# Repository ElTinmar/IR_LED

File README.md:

# IR_LED

This is an open-source infra-red illumnination solution (LED panel and driver) for machine vision.
An arduino nano every sits at the core of the driver board, and allows remote control from a PC through serial communication

The main features are: 

- infra-red LED panel, with 3 separately addressable concentric rings  
- manual or remote control of the brightness for the 3 channels
- LED driver can be strobed with the open-collector trigger output of a machine vision camera,
which significantly reduces heat output
- the temperature of the LED panel is measured in real time and can by controlled with a fan. 
The fan PWM can be set manually or via a software PID controller on the arduino

## hardware

PCB design files (Kicad v10)

## firmware

Arduino code (Arduino Nano Every)
 
## software

Python driver and GUI on the PC side

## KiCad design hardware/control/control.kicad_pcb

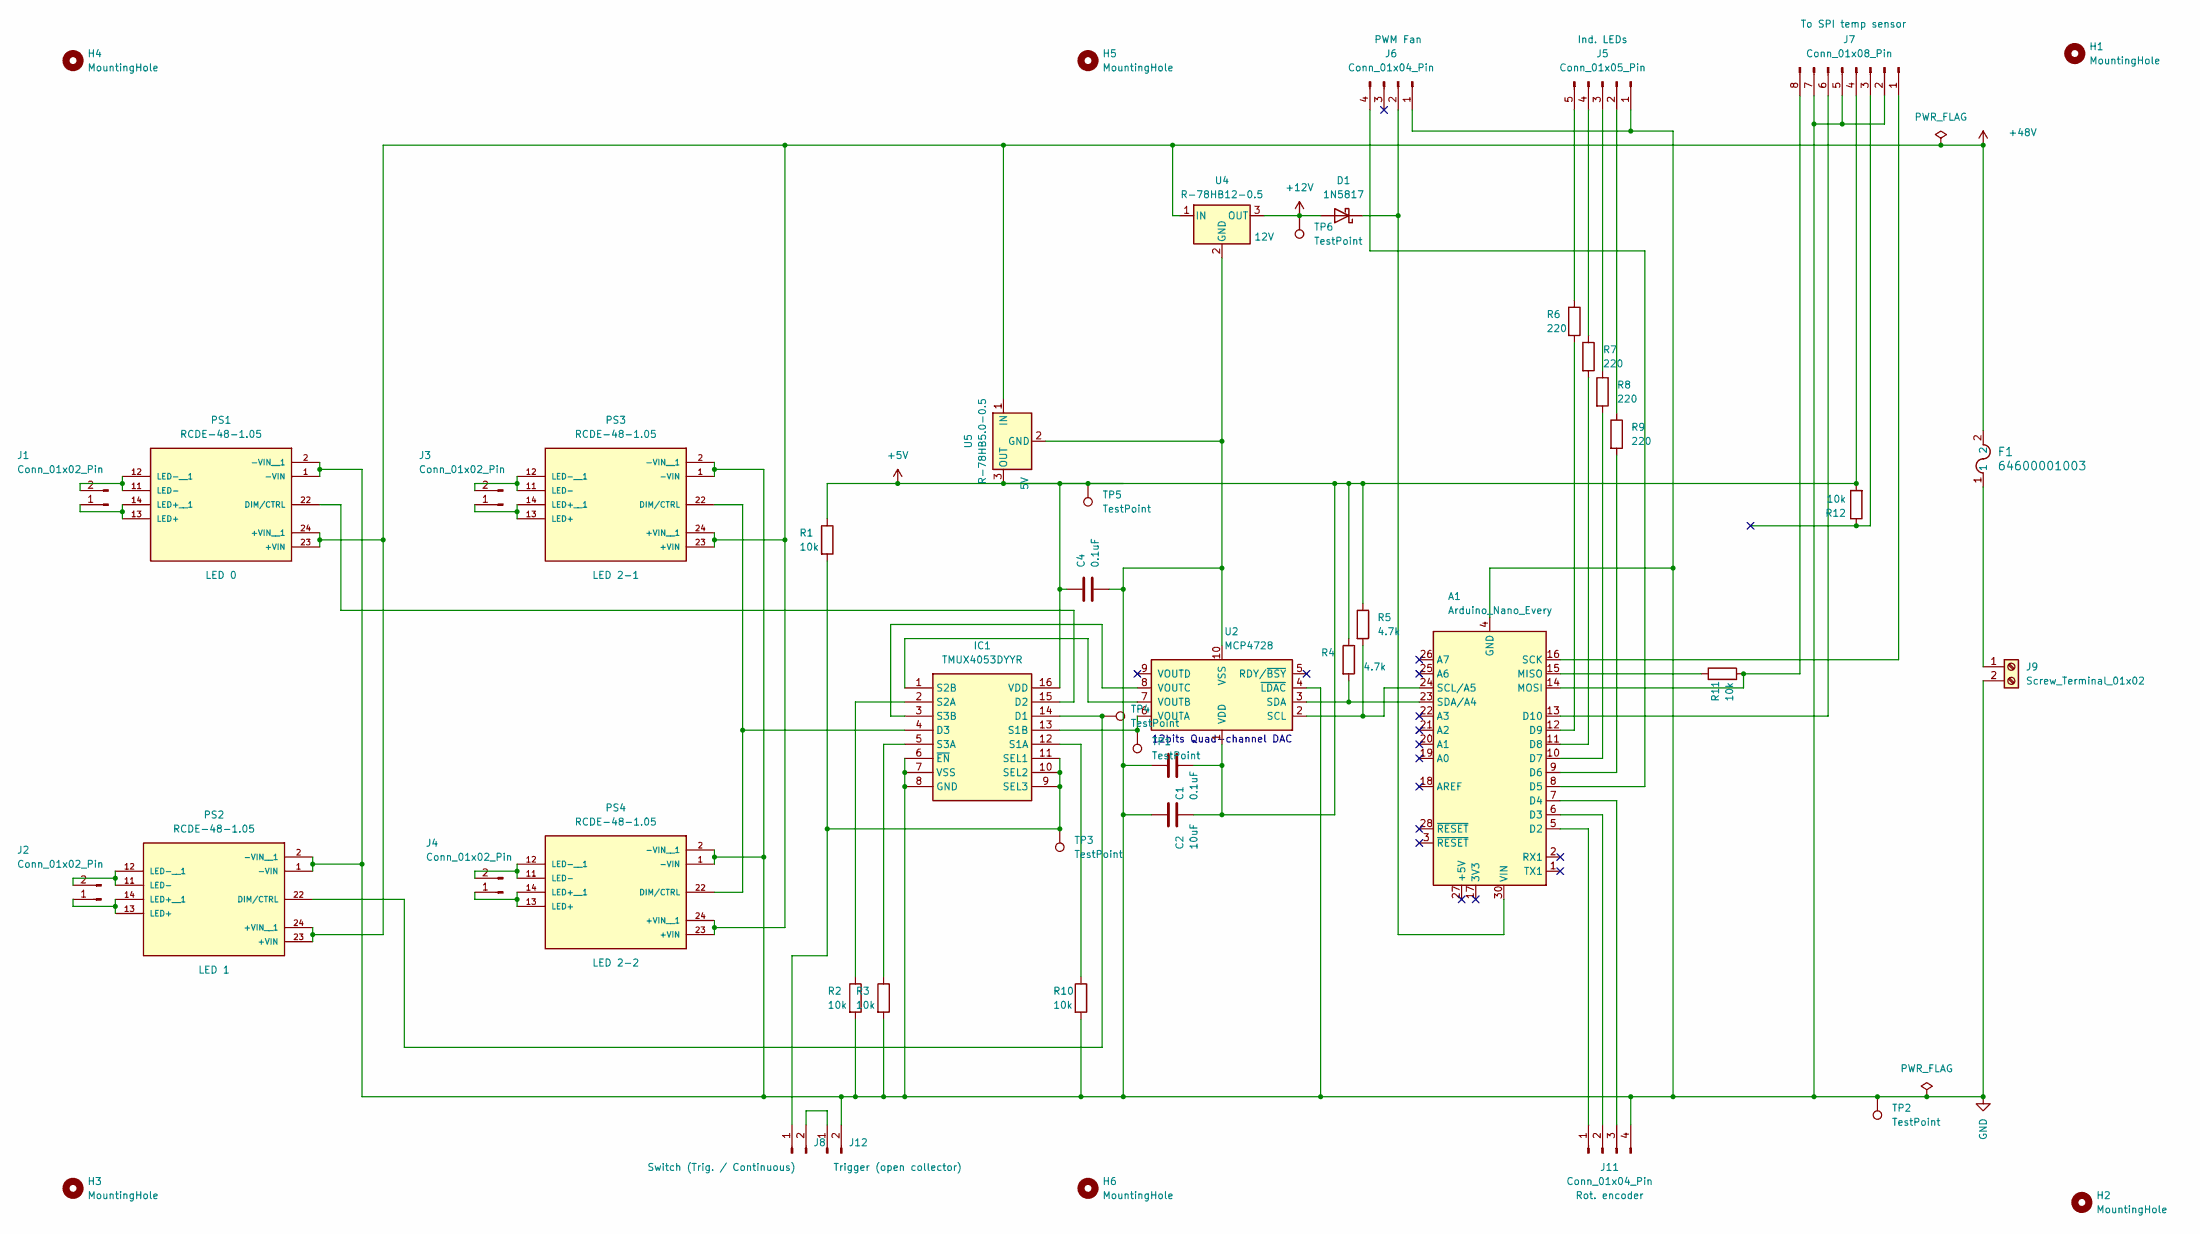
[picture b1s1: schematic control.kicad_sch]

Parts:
A1: Arduino_Nano_Every; Arduino_Nano
C1, C4: 0.1uF; C_Disc_D5.0mm_W2.5mm_P2.50mm
C2: 10uF; C_Disc_D5.0mm_W2.5mm_P2.50mm
D1: 1N5817; D_DO-41_SOD81_P10.16mm_Horizontal
F1: 64600001003; FUSE_646_1_LTF
H1, H2, H3, H4, H5, H6: MountingHole; MountingHole_3.2mm_M3
IC1: TMUX4053DYYR; SOP50P326X110-16N; Mouser Part Number 595-TMUX4053DYYR
J1, J2, J3, J4: Conn_01x02_Pin; Molex_Micro-Fit_3.0_43650-0200_1x02_P3.00mm_Horizontal
J5: Conn_01x05_Pin; Molex_KK-254_AE-6410-05A_1x05_P2.54mm_Vertical
J6, J11: Conn_01x04_Pin; Molex_KK-254_AE-6410-04A_1x04_P2.54mm_Vertical
J7: Conn_01x08_Pin; Molex_PicoBlade_53047-0810_1x08_P1.25mm_Vertical
J8, J12: Camera Isolated triggers (open collector); Molex_KK-254_AE-6410-02A_1x02_P2.54mm_Vertical
J9: Screw_Terminal_01x02; TerminalBlock_Phoenix_MKDS-1,5-2-5.08_1x02_P5.08mm_Horizont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
PS1, PS2, PS3, PS4: RCDE-48-1.05; CONV_RCDE-48-1.05; PARTREV 0/2019
R1, R2, R3, R10, R11, R12: 10k; R_Axial_DIN0207_L6.3mm_D2.5mm_P10.16mm_Horizontal
R4, R5: 4.7k; R_Axial_DIN0207_L6.3mm_D2.5mm_P10.16mm_Horizontal
R6, R7, R8, R9: 220; R_Axial_DIN0207_L6.3mm_D2.5mm_P10.16mm_Horizontal
TP1, TP2, TP3, TP4, TP5, TP6: TestPoint; TestPoint_Pad_D2.0mm
U2: MCP4728; MSOP-10_3x3mm_P0.5mm
U4: R-78HB12-0.5; Converter_DCDC_RECOM_R-78HB-0.5_THT
U5: R-78HB5.0-0.5; Converter_DCDC_RECOM_R-78HB-0.5_THT

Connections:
+5V: C1.2, C2.2, C4.1, IC1.16 (VDD), J7.4, R1.1, R4.1, R5.1, R12.2, TP5.1 (1_1), U2.1 (VDD), U5.3 (OUT)
+12V: D1.2 (A), TP6.1 (1_1), U4.3 (OUT)
+48V: F1.2, PS1.23 (+VIN), PS1.24 (+VIN__1), PS2.23 (+VIN), PS2.24 (+VIN__1), PS3.23 (+VIN), PS3.24 (+VIN__1), PS4.23 (+VIN), PS4.24 (+VIN__1), U4.1 (IN), U5.1 (IN)
GND: A1.4 (GND), A1.29 (GND), C1.1, C2.1, C4.2, IC1.6 (~EN), IC1.7 (VSS), IC1.8 (GND), J5.1, J6.1, J7.2, J7.5, J7.7, J9.2, J11.4, J12.2, PS1.1 (-VIN), PS1.2 (-VIN__1), PS2.1 (-VIN), PS2.2 (-VIN__1), PS3.1 (-VIN), PS3.2 (-VIN__1), PS4.1 (-VIN), PS4.2 (-VIN__1), R2.2, R3.2, R10.2, TP2.1 (1_1), U2.4 (~LDAC), U2.10 (VSS), U4.2 (GND), U5.2 (GND)
unnamed: A1.5 (D2), J11.1
unnamed: A1.6 (D3), J11.2
unnamed: A1.7 (D4), J11.3
unnamed: A1.8 (D5), J6.4
unnamed: A1.9 (D6), R9.2
unnamed: A1.10 (D7), R8.2
unnamed: A1.11 (D8), R7.2
unnamed: A1.12 (D9), R6.2
unnamed: A1.13 (D10), J7.6
unnamed: A1.15 (MISO), R11.1
unnamed: A1.14 (MOSI), J7.8, R11.2
unnamed: A1.16 (SCK), J7.1
unnamed: A1.24 (SCL/A5), R5.2, U2.2 (SCL)
unnamed: A1.23 (SDA/A4), R4.2, U2.3 (SDA)
unnamed: A1.30 (VIN), D1.1 (K), J6.2
unnamed: IC1.14 (D1), PS2.22 (DIM/CTRL), TP4.1 (1_1)
unnamed: IC1.15 (D2), PS1.22 (DIM/CTRL)
unnamed: IC1.4 (D3), PS3.22 (DIM/CTRL), PS4.22 (DIM/CTRL)
unnamed: IC1.12 (S1A), R10.1
unnamed: IC1.13 (S1B), TP1.1 (1_1), U2.6 (VOUTA)
unnamed: IC1.2 (S2A), R2.1
unnamed: IC1.1 (S2B), U2.7 (VOUTB)
unnamed: IC1.5 (S3A), R3.1
unnamed: IC1.3 (S3B), U2.8 (VOUTC)
unnamed: IC1.9 (SEL3), IC1.10 (SEL2), IC1.11 (SEL1), J8.1, R1.2, TP3.1 (1_1)
unnamed: J1.1, PS1.13 (LED+), PS1.14 (LED+__1)
unnamed: J1.2, PS1.11 (LED-), PS1.12 (LED-__1)
unnamed: J2.1, PS2.13 (LED+), PS2.14 (LED+__1)
unnamed: J2.2, PS2.11 (LED-), PS2.12 (LED-__1)
unnamed: J3.1, PS3.13 (LED+), PS3.14 (LED+__1)
unnamed: J3.2, PS3.11 (LED-), PS3.12 (LED-__1)
unnamed: J4.1, PS4.13 (LED+), PS4.14 (LED+__1)
unnamed: J4.2, PS4.11 (LED-), PS4.12 (LED-__1)
unnamed: J5.2, R9.1
unnamed: J5.3, R8.1
unnamed: J5.4, R7.1
unnamed: J5.5, R6.1
unnamed: F1.1, J9.1
unnamed: J8.2, J12.1

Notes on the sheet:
12bits Quad-channel DAC

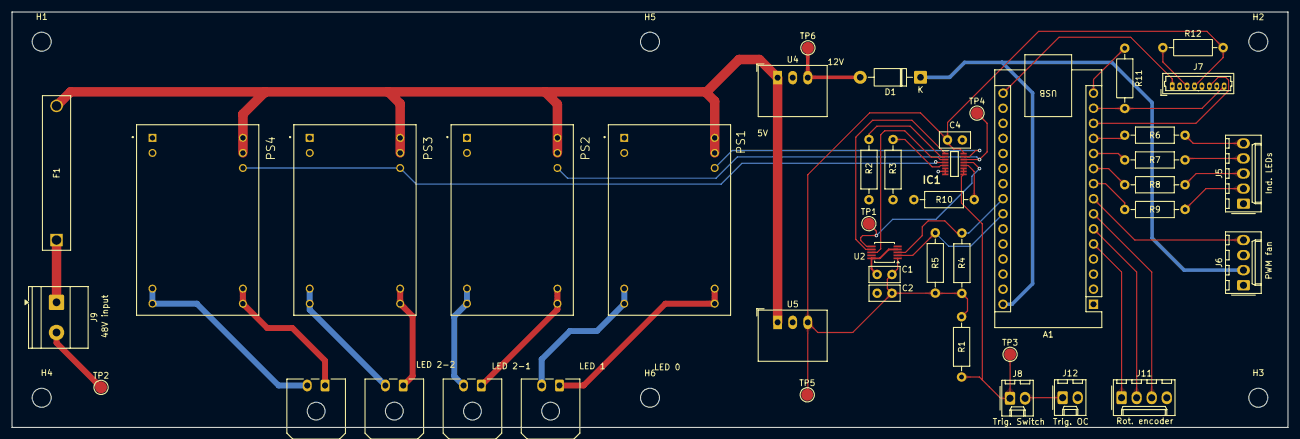
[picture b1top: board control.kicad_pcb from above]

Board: 2 copper layers, 215.0 x 70.0 mm, 49 parts (0 on the bottom side), 43 nets.

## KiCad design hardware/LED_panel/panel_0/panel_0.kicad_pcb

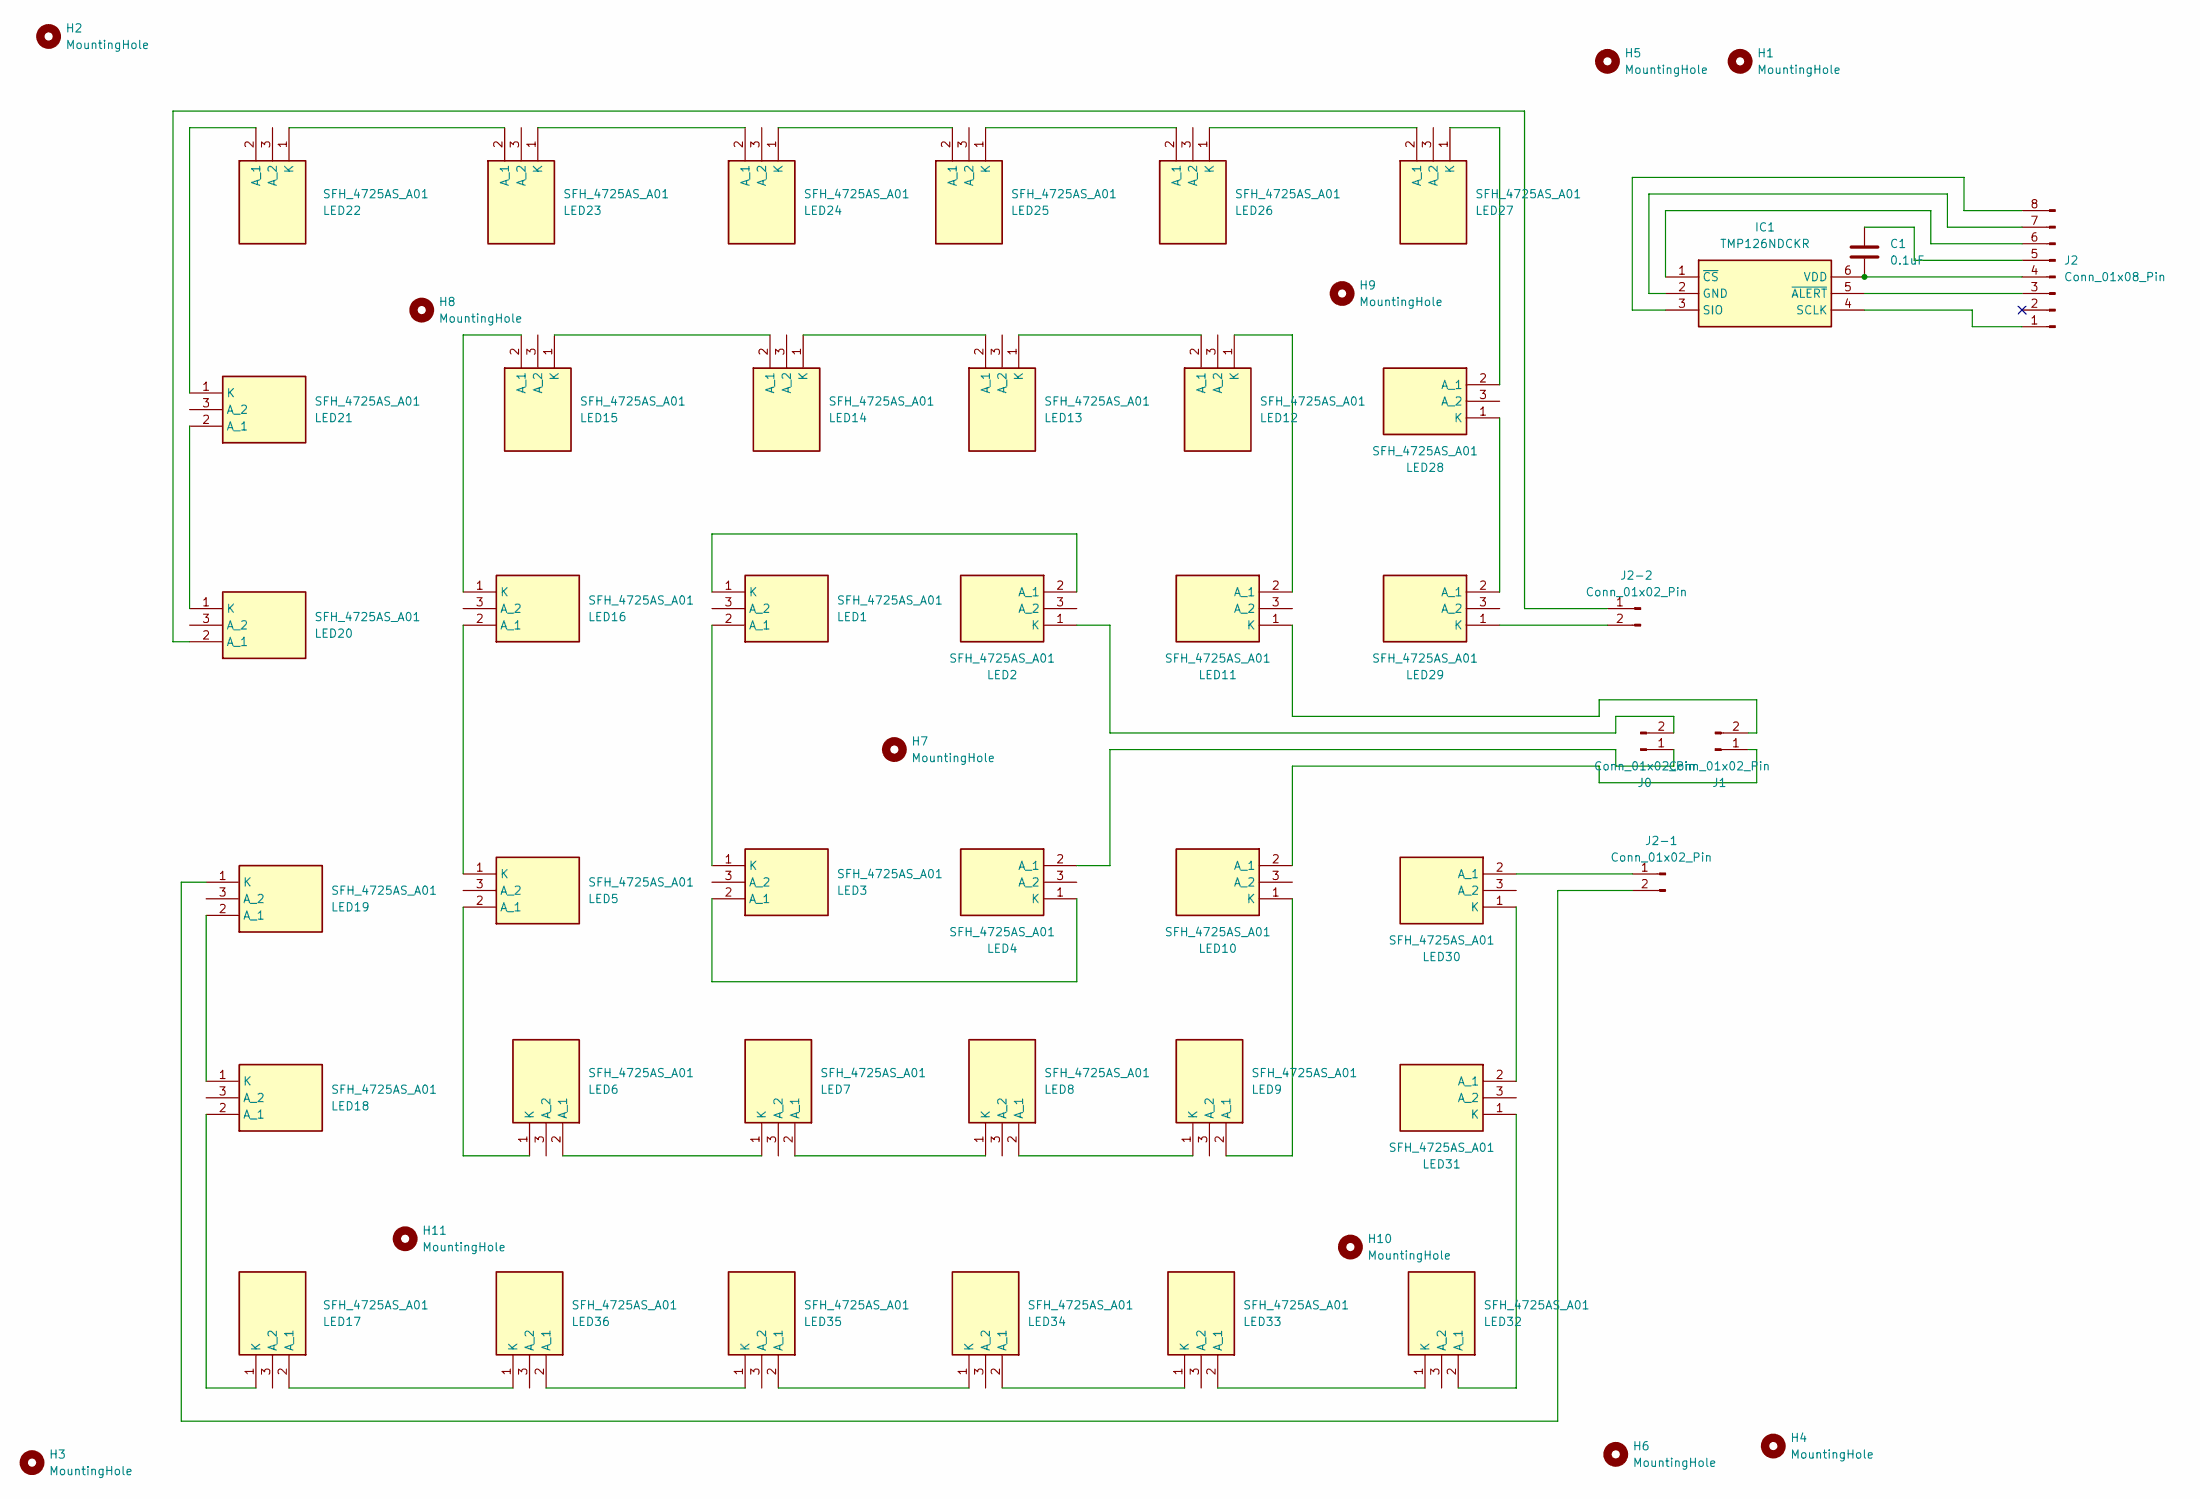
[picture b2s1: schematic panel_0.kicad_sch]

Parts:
C1: 0.1uF; C_0805_2012Metric
H1, H2, H3, H4, H5, H6: MountingHole; MountingHole_3.2mm_M3
H7, H8, H9, H10, H11: MountingHole; MountingHole_2.2mm_M2
IC1: TMP126NDCKR; SOT65P210X110-6N; Mouser Part Number 595-TMP126NDCKR
J0, J1, J2-1, J2-2: Conn_01x02_Pin; Molex_Micro-Fit_3.0_43650-0224_1x02-1MP_P3.00mm_Vertical
J2: Conn_01x08_Pin; Molex_PicoBlade_53261-0871_1x08-1MP_P1.25mm_Horizontal
LED1, LED2, LED3, LED4, LED5, LED6, LED7, LED8, LED9, LED10, LED11, LED12, LED13, LED14, LED15, LED16, LED17, LED18, LED19, LED20, LED21, LED22, LED23, LED24, LED25, LED26, LED27, LED28, LED29, LED30, LED31, LED32, LED33, LED34, LED35, LED36: SFH_4725AS_A01; SFH4725ASA01; Manufacturer_Part_Number SFH 4725AS A01

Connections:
unnamed: IC1.2 (GND), J2.7
unnamed: IC1.4 (SCLK), J2.1
unnamed: IC1.3 (SIO), J2.8
unnamed: C1.2, IC1.6 (VDD), J2.4
unnamed: IC1.5 (~ALERT), J2.3
unnamed: IC1.1 (~CS), J2.6
unnamed: J0.1, LED4.2 (A_1)
unnamed: J0.2, LED2.1 (K)
unnamed: J1.1, LED10.2 (A_1)
unnamed: J1.2, LED11.1 (K)
unnamed: J2-1.1, LED30.2 (A_1)
unnamed: J2-1.2, LED19.1 (K)
unnamed: J2-2.1, LED20.2 (A_1)
unnamed: J2-2.2, LED29.1 (K)
unnamed: C1.1, J2.5
unnamed: LED1.2 (A_1), LED3.1 (K)
unnamed: LED1.1 (K), LED2.2 (A_1)
unnamed: LED3.2 (A_1), LED4.1 (K)
unnamed: LED5.2 (A_1), LED6.1 (K)
unnamed: LED6.2 (A_1), LED7.1 (K)
unnamed: LED7.2 (A_1), LED8.1 (K)
unnamed: LED8.2 (A_1), LED9.1 (K)
unnamed: LED9.2 (A_1), LED10.1 (K)
unnamed: LED11.2 (A_1), LED12.1 (K)
unnamed: LED12.2 (A_1), LED13.1 (K)
unnamed: LED13.2 (A_1), LED14.1 (K)
unnamed: LED14.2 (A_1), LED15.1 (K)
unnamed: LED15.2 (A_1), LED16.1 (K)
unnamed: LED5.1 (K), LED16.2 (A_1)
unnamed: LED17.2 (A_1), LED36.1 (K)
unnamed: LED17.1 (K), LED18.2 (A_1)
unnamed: LED18.1 (K), LED19.2 (A_1)
unnamed: LED20.1 (K), LED21.2 (A_1)
unnamed: LED21.1 (K), LED22.2 (A_1)
unnamed: LED22.1 (K), LED23.2 (A_1)
unnamed: LED23.1 (K), LED24.2 (A_1)
unnamed: LED24.1 (K), LED25.2 (A_1)
unnamed: LED25.1 (K), LED26.2 (A_1)
unnamed: LED26.1 (K), LED27.2 (A_1)
unnamed: LED27.1 (K), LED28.2 (A_1)
unnamed: LED28.1 (K), LED29.2 (A_1)
unnamed: LED30.1 (K), LED31.2 (A_1)
unnamed: LED31.1 (K), LED32.2 (A_1)
unnamed: LED32.1 (K), LED33.2 (A_1)
unnamed: LED33.1 (K), LED34.2 (A_1)
unnamed: LED34.1 (K), LED35.2 (A_1)
unnamed: LED35.1 (K), LED36.2 (A_1)

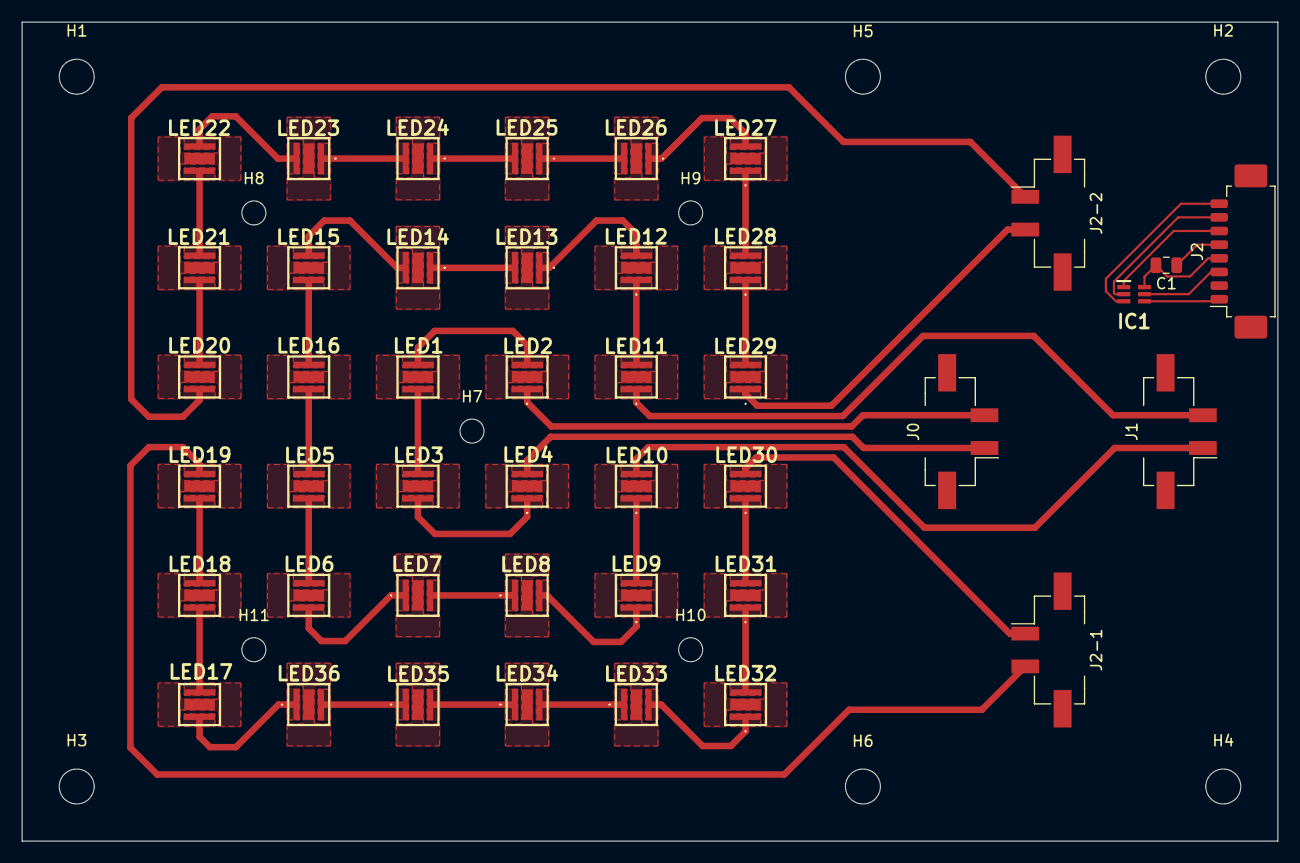
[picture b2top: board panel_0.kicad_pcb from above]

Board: 2 copper layers, 115.0 x 75.0 mm, 54 parts (0 on the bottom side), 47 nets.

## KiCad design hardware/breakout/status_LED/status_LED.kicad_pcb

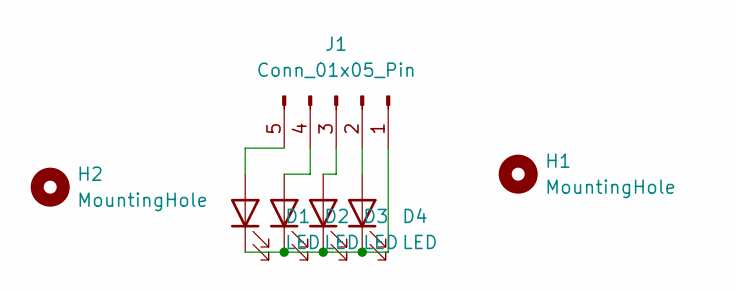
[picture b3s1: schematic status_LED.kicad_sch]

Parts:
D1, D2, D3, D4: LED; LED_D5.0mm
H1, H2: MountingHole; MountingHole_2.2mm_M2
J1: Conn_01x05_Pin; Molex_KK-254_AE-6410-05A_1x05_P2.54mm_Vertical

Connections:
unnamed: D1.2 (A), J1.5
unnamed: D1.1 (K), D2.1 (K), D3.1 (K), D4.1 (K), J1.1
unnamed: D2.2 (A), J1.4
unnamed: D3.2 (A), J1.3
unnamed: D4.2 (A), J1.2

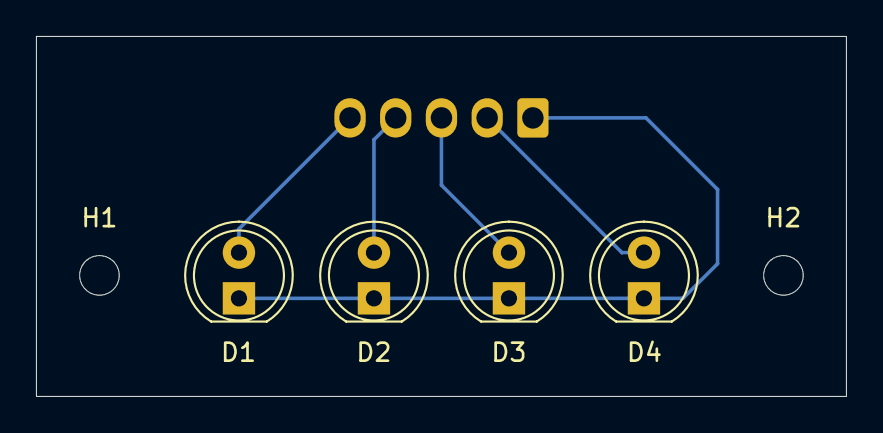
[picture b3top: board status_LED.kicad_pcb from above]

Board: 2 copper layers, 45.0 x 20.0 mm, 7 parts (1 on the bottom side), 5 nets.

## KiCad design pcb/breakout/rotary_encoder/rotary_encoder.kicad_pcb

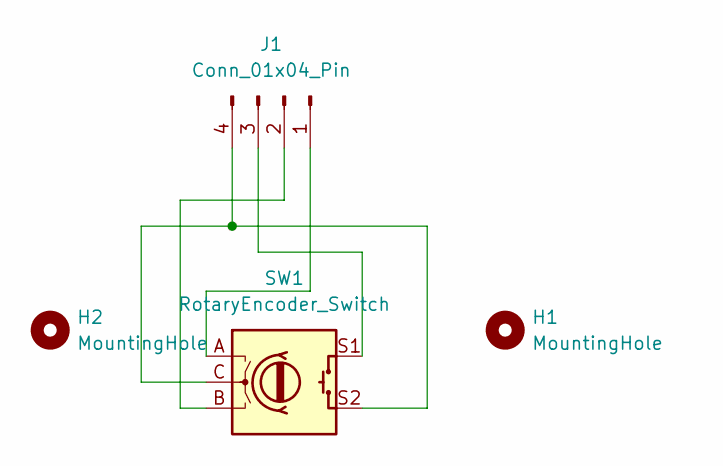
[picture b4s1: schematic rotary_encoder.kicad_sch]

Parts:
H1, H2: MountingHole; MountingHole_2.2mm_M2
J1: Conn_01x04_Pin; Molex_KK-254_AE-6410-04A_1x04_P2.54mm_Vertical
SW1: RotaryEncoder_Switch; RotaryEncoder_Alps_EC11E-Switch_Vertical_H20mm

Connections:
unnamed: J1.1, SW1.A
unnamed: J1.2, SW1.B
unnamed: J1.3, SW1.S1
unnamed: J1.4, SW1.C, SW1.S2

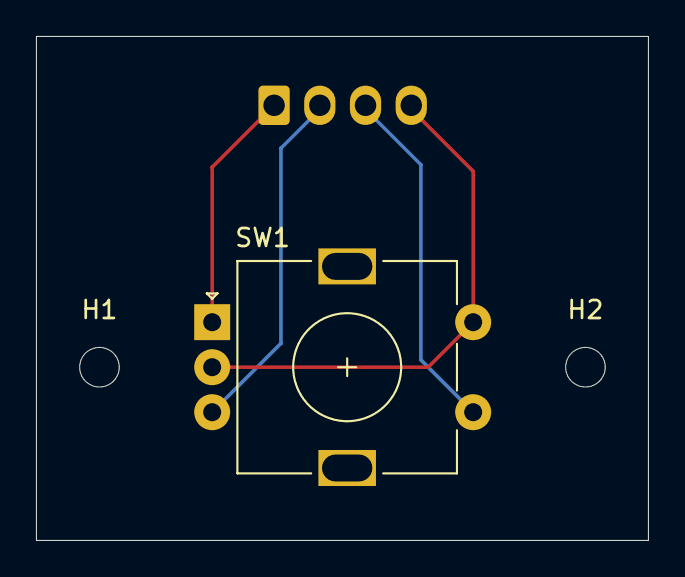
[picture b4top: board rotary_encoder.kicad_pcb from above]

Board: 2 copper layers, 34.0 x 28.0 mm, 4 parts (1 on the bottom side), 4 nets.

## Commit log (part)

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2026-06-11 adding files
2026-06-11 changed folder name
2026-06-11 bare minimum
2026-06-11 added files
2026-06-11 add file
2026-06-11 25kHz pwm for fan ctrl
2026-06-11 add flag verbosity
2026-06-11 comments timer
2026-06-11 update gitignore python
2026-06-12 dont sync lib path
2026-06-12 remove lib path
2026-06-12 add spi temp board and connector
2026-06-12 removing old thermocouple ic
2026-06-12 external spi temp chip
2026-06-12 added alert pullup
2026-06-12 added extra mounting points
2026-06-12 rework pcb layout
2026-06-12 remove low level readmes
2026-06-15 removing 90deg turns
2026-06-15 silkscreen r1
2026-06-15 teardrops
2026-06-15 cleaning traces
2026-06-15 changed molex connector
